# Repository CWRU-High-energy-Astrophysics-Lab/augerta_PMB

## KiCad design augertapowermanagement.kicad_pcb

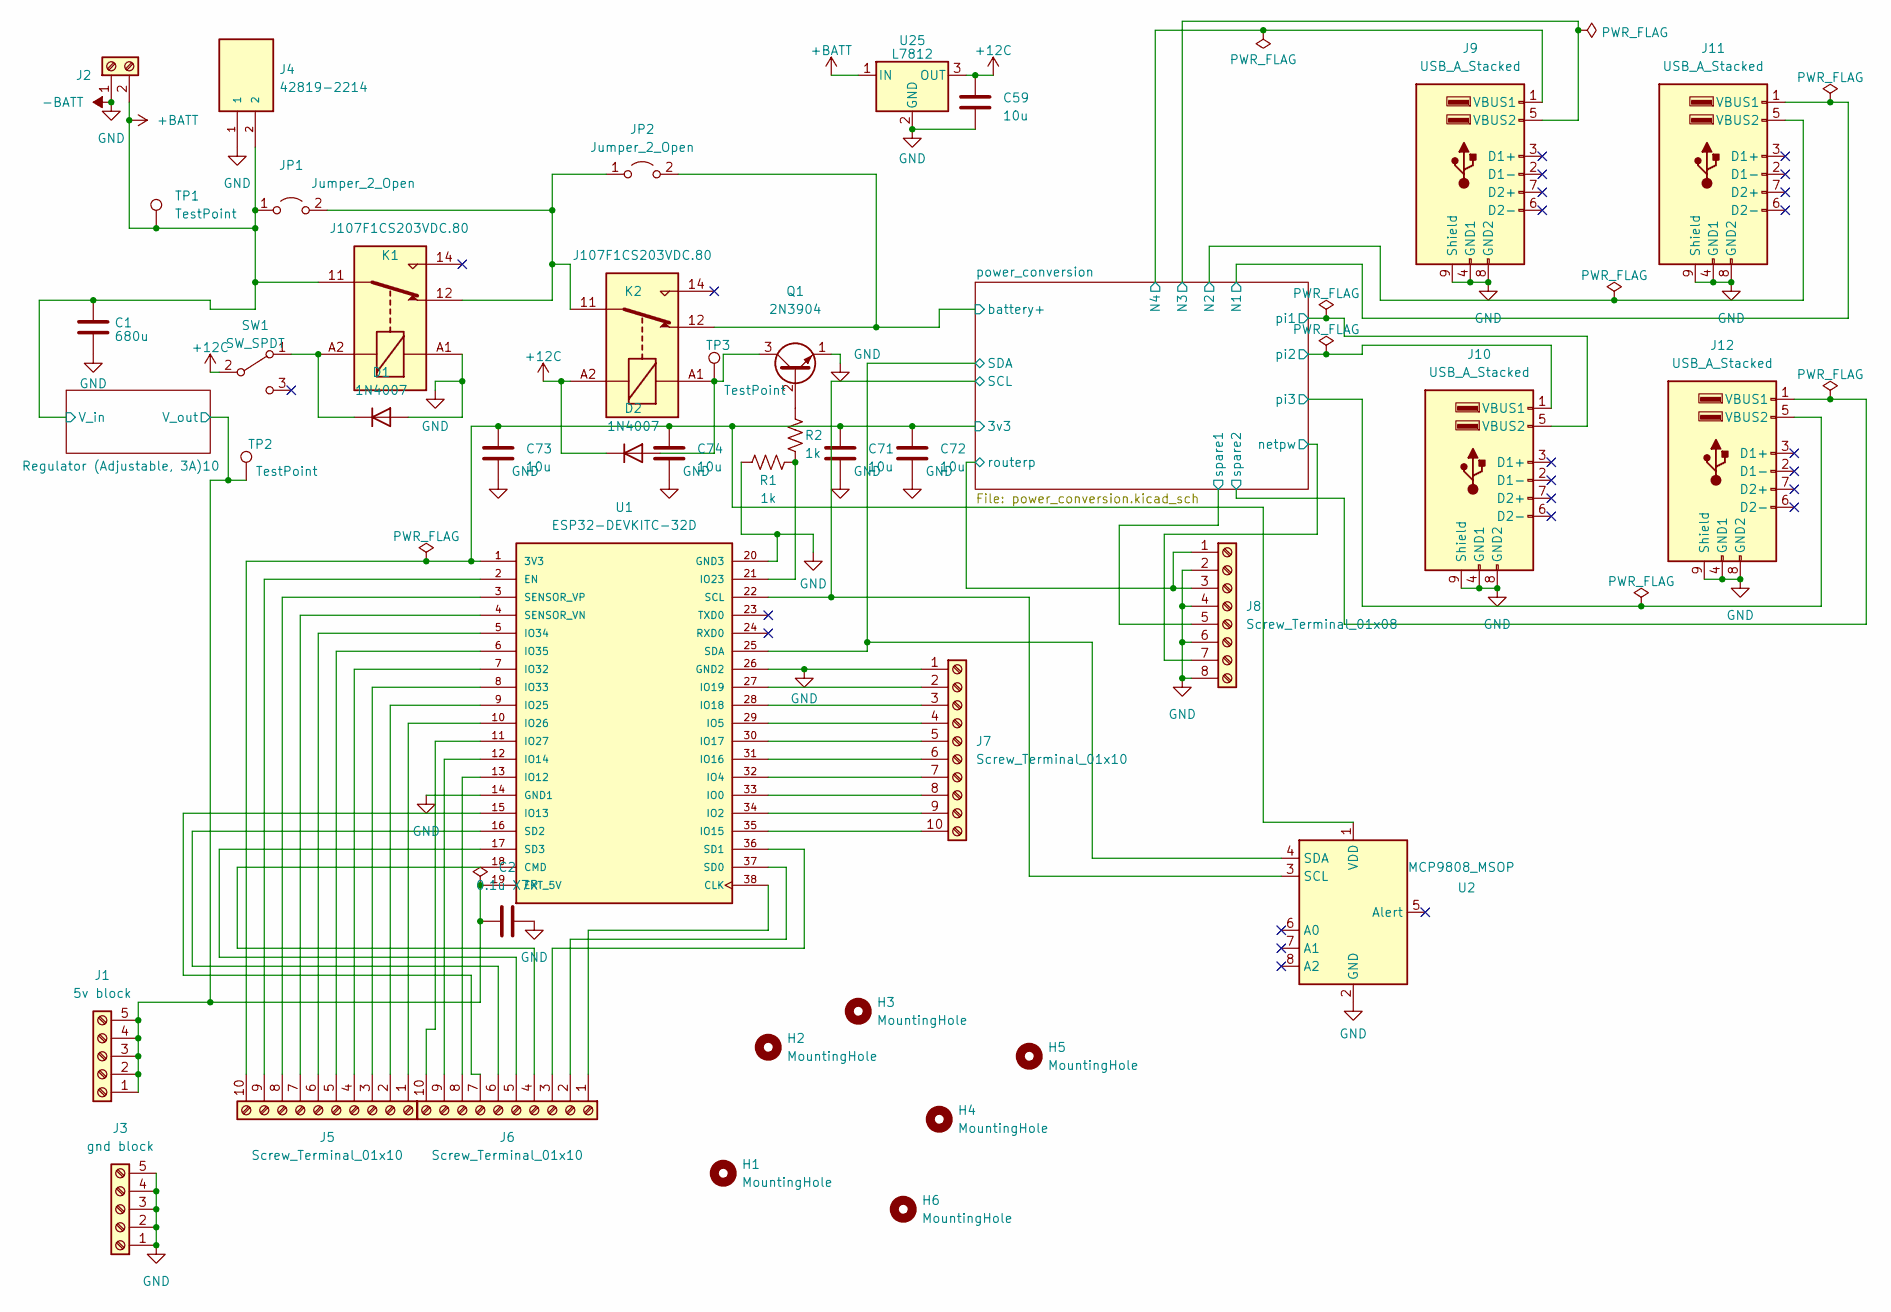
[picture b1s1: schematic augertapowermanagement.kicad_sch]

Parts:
C1: 680u; CP_Radial_D35.0mm_P10.00mm_SnapIn
C2: 0.1u X7R; C_1210_3225Metric_Pad1.33x2.70mm_HandSolder
C59, C71, C72, C73, C74: 10u; C_1210_3225Metric_Pad1.33x2.70mm_HandSolder
D1, D2: 1N4007; D_DO-41_SOD81_P10.16mm_Horizontal
H1, H2, H3, H4, H5, H6: MountingHole; MountingHole_2.5mm
J1: 5v block; TerminalBlock_Phoenix_MKDS-1,5-5-5.08_1x05_P5.08mm_Horizont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
J2: Battery in; TerminalBlock_Phoenix_MKDS-1,5-2-5.08_1x02_P5.08mm_Horizont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
J3: gnd block; TerminalBlock_Phoenix_MKDS-1,5-5-5.08_1x05_P5.08mm_Horizont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
J4: 42819-2214; Molex_Mini-Fit_Sr_42819-22XX_1x02_P10.00mm_Vertical_Thermal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; PARTREV D
J5, J6, J7: Screw_Terminal_01x10; TerminalBlock_Phoenix_MKDS-1,5-10-5.08_1x10_P5.08mm_Horizon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
J8: Screw_Terminal_01x08; TerminalBlock_Phoenix_PT-1,5-8-5.0-H_1x08_P5.00mm_Horizontal
J9, J10, J11, J12: USB_A_Stacked; USB_A_Wuerth_61400826021_Horizontal_Stacked
JP1, JP2: Jumper_2_Open; JUMPER_5102TR
K1, K2: J107F1CS203VDC.80; Relay_SPDT_RAYEX-L90S
Q1: 2N3904; TO-92_HandSolder
R1, R2: 1k; R_1206_3216Metric_Pad1.30x1.75mm_HandSolder
SW1: SW_SPDT; SW_CuK_OS102011MA1QN1_SPDT_Angled
TP1, TP2, TP3: TestPoint; TestPoint_Plated_Hole_D2.0mm
U1: ESP32-DEVKITC-32D; MODULE_ESP32-DEVKITC-32D; PARTREV 4
U2: MCP9808_MSOP; PinSocket_1x08_P2.54mm_Vertical
U25: L7812; TO-220-3_Horizontal_TabDown

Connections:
+12C: C59.1, D2.1 (K), K2.A2, SW1.2 (B), U25.3 (OUT)
-BATT: C1.2, C2.2, C59.2, C71.2, C72.2, C73.2, C74.2, D1.2 (A), J2.1, J3.1, J3.2, J3.3, J3.4, J3.5, J4.1, J7.1, J8.2, J8.4, J8.6, J8.8, J9.4 (GND1), J9.8 (GND2), J9.9 (Shield), J10.4 (GND1), J10.8 (GND2), J10.9 (Shield), J11.4 (GND1), J11.8 (GND2), J11.9 (Shield), J12.4 (GND1), J12.8 (GND2), J12.9 (Shield), K1.A1, Q1.1 (E), R1.1, U1.14 (GND1), U1.20 (GND3), U1.26 (GND2), U2.2 (GND), U25.2 (GND); also elsewhere on the board
/Regulator (Adjustable, 3A)10/V_out: C2.1, J1.1, J1.2, J1.3, J1.4, J1.5, TP2.1, U1.19 (EXT_5V); also elsewhere on the board
/power_conversion/3v3: C71.1, C72.1, C73.1, C74.1, J5.10, U1.1 (3V3), U2.1 (VDD); also elsewhere on the board
/power_conversion/N1: J11.1 (VBUS1); also elsewhere on the board
/power_conversion/N2: J11.5 (VBUS2); also elsewhere on the board
/power_conversion/N3: J9.5 (VBUS2); also elsewhere on the board
/power_conversion/N4: J9.1 (VBUS1); also elsewhere on the board
/power_conversion/SCL: U1.22 (SCL), U2.3 (SCL); also elsewhere on the board
/power_conversion/SDA: U1.25 (SDA), U2.4 (SDA); also elsewhere on the board
/power_conversion/netpw: J8.7; also elsewhere on the board
/power_conversion/pi1: J10.5 (VBUS2); also elsewhere on the board
/power_conversion/pi2: J10.1 (VBUS1); also elsewhere on the board
/power_conversion/pi3: J12.5 (VBUS2); also elsewhere on the board
/power_conversion/routerp: J8.1, J8.3; also elsewhere on the board
/power_conversion/spare1: J8.5; also elsewhere on the board
/power_conversion/spare2: J12.1 (VBUS1); also elsewhere on the board
unnamed: D1.1 (K), K1.A2, SW1.1 (A)
unnamed: D2.2 (A), K2.A1, Q1.3 (C), TP3.1
unnamed: J5.1, U1.10 (IO26)
unnamed: J5.2, U1.9 (IO25)
unnamed: J5.3, U1.8 (IO33)
unnamed: J5.4, U1.7 (IO32)
unnamed: J5.5, U1.6 (IO35)
unnamed: J5.6, U1.5 (IO34)
unnamed: J5.7, U1.4 (SENSOR_VN)
unnamed: J5.8, U1.3 (SENSOR_VP)
unnamed: J5.9, U1.2 (EN)
unnamed: J6.1, U1.38 (CLK)
unnamed: J6.2, U1.37 (SD0)
unnamed: J6.3, U1.36 (SD1)
unnamed: J6.4, U1.18 (CMD)
unnamed: J6.5, U1.17 (SD3)
unnamed: J6.6, U1.16 (SD2)
unnamed: J6.7, U1.15 (IO13)
unnamed: J6.8, U1.13 (IO12)
unnamed: J6.9, U1.12 (IO14)
unnamed: J6.10, U1.11 (IO27)
unnamed: J7.2, U1.27 (IO19)
unnamed: J7.3, U1.28 (IO18)
unnamed: J7.4, U1.29 (IO5)
unnamed: J7.5, U1.30 (IO17)
unnamed: J7.6, U1.31 (IO16)
unnamed: J7.7, U1.32 (IO4)
unnamed: J7.8, U1.33 (IO0)
unnamed: J7.9, U1.34 (IO2)
unnamed: J7.10, U1.35 (IO15)
unnamed: JP1.2 (B), JP2.1 (A), K1.12, K2.11
unnamed: Q1.2 (B), R2.2
unnamed: R1.2, R2.1, U1.21 (IO23)

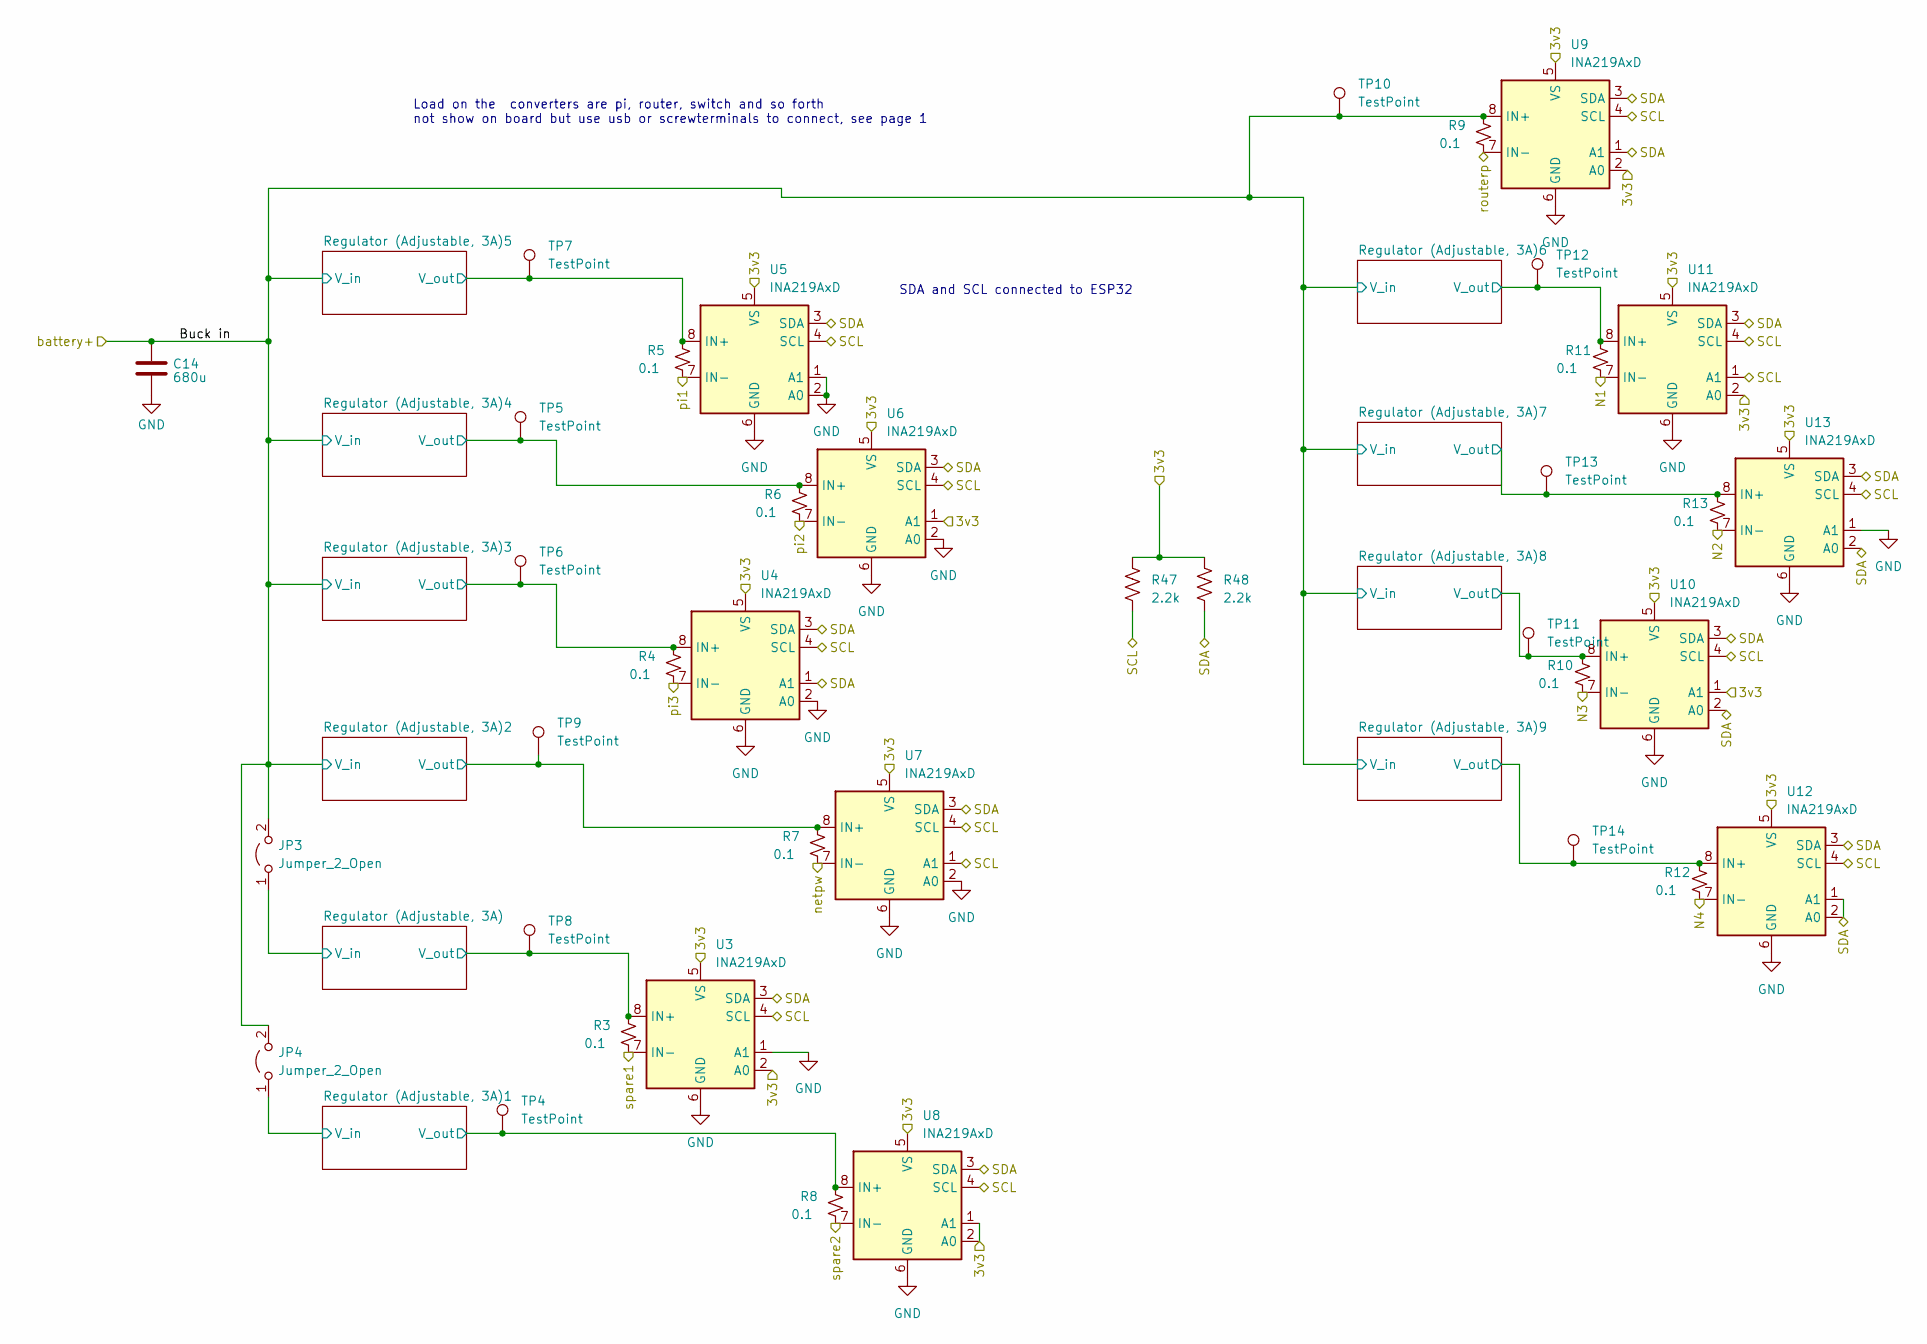
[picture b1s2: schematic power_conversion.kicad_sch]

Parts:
C14: 680u; CP_Radial_D35.0mm_P10.00mm_SnapIn
JP3, JP4: Jumper_2_Open; PinHeader_1x02_P2.00mm_Horizontal
R3, R4, R5, R6, R7, R8, R9, R10, R11, R12, R13: 0.1; R_2816_7142Metric_Pad3.20x4.45mm_HandSolder
R47, R48: 2.2k; R_1210_3225Metric_Pad1.30x2.65mm_HandSolder
TP4, TP5, TP6, TP7, TP8, TP9, TP10, TP11, TP12, TP13, TP14: TestPoint; TestPoint_Plated_Hole_D2.0mm
U3, U4, U5, U6, U7, U8, U9, U10, U11, U12, U13: INA219AxD; SOIC-8_3.9x4.9mm_P1.27mm

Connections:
-BATT: C14.2, U3.1 (A1), U3.6 (GND), U4.2 (A0), U4.6 (GND), U5.1 (A1), U5.2 (A0), U5.6 (GND), U6.2 (A0), U6.6 (GND), U7.2 (A0), U7.6 (GND), U8.6 (GND), U9.6 (GND), U10.6 (GND), U11.6 (GND), U12.6 (GND), U13.1 (A1), U13.6 (GND); also elsewhere on the board
/power_conversion/3v3: R47.1, R48.1, U3.2 (A0), U3.5 (VS), U4.5 (VS), U5.5 (VS), U6.1 (A1), U6.5 (VS), U7.5 (VS), U8.1 (A1), U8.2 (A0), U8.5 (VS), U9.2 (A0), U9.5 (VS), U10.1 (A1), U10.5 (VS), U11.2 (A0), U11.5 (VS), U12.5 (VS), U13.5 (VS); also elsewhere on the board
/power_conversion/N1: R11.1, U11.7 (IN-); also elsewhere on the board
/power_conversion/N2: R13.1, U13.7 (IN-); also elsewhere on the board
/power_conversion/N3: R10.1, U10.7 (IN-); also elsewhere on the board
/power_conversion/N4: R12.1, U12.7 (IN-); also elsewhere on the board
/power_conversion/Regulator (Adjustable, 3A)1/V_in: JP4.1 (A); also elsewhere on the board
/power_conversion/Regulator (Adjustable, 3A)1/V_out: R8.2, TP4.1, U8.8 (IN+); also elsewhere on the board
/power_conversion/Regulator (Adjustable, 3A)2/V_out: R7.2, TP9.1, U7.8 (IN+); also elsewhere on the board
/power_conversion/Regulator (Adjustable, 3A)3/V_out: R4.2, TP6.1, U4.8 (IN+); also elsewhere on the board
/power_conversion/Regulator (Adjustable, 3A)5/V_out: R5.2, TP7.1, U5.8 (IN+); also elsewhere on the board
/power_conversion/Regulator (Adjustable, 3A)6/V_out: R11.2, TP12.1, U11.8 (IN+); also elsewhere on the board
/power_conversion/Regulator (Adjustable, 3A)7/V_out: R13.2, TP13.1, U13.8 (IN+); also elsewhere on the board
/power_conversion/Regulator (Adjustable, 3A)8/V_out: R10.2, TP11.1, U10.8 (IN+); also elsewhere on the board
/power_conversion/Regulator (Adjustable, 3A)9/V_out: R12.2, TP14.1, U12.8 (IN+); also elsewhere on the board
/power_conversion/Regulator (Adjustable, 3A)/V_in: JP3.1 (A); also elsewhere on the board
/power_conversion/Regulator (Adjustable, 3A)/V_out: R3.2, TP8.1, U3.8 (IN+); also elsewhere on the board
/power_conversion/SCL: R47.2, U3.4 (SCL), U4.4 (SCL), U5.4 (SCL), U6.4 (SCL), U7.1 (A1), U7.4 (SCL), U8.4 (SCL), U9.4 (SCL), U10.4 (SCL), U11.1 (A1), U11.4 (SCL), U12.4 (SCL), U13.4 (SCL); also elsewhere on the board
/power_conversion/SDA: R48.2, U3.3 (SDA), U4.1 (A1), U4.3 (SDA), U5.3 (SDA), U6.3 (SDA), U7.3 (SDA), U8.3 (SDA), U9.1 (A1), U9.3 (SDA), U10.2 (A0), U10.3 (SDA), U11.3 (SDA), U12.1 (A1), U12.2 (A0), U12.3 (SDA), U13.2 (A0), U13.3 (SDA); also elsewhere on the board
/power_conversion/netpw: R7.1, U7.7 (IN-); also elsewhere on the board
/power_conversion/pi1: R5.1, U5.7 (IN-); also elsewhere on the board
/power_conversion/pi2: R6.1, U6.7 (IN-); also elsewhere on the board
/power_conversion/pi3: R4.1, U4.7 (IN-); also elsewhere on the board
/power_conversion/routerp: R9.1, U9.7 (IN-); also elsewhere on the board
/power_conversion/spare1: R3.1, U3.7 (IN-); also elsewhere on the board
/power_conversion/spare2: R8.1, U8.7 (IN-); also elsewhere on the board

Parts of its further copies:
C3: 680u; CP_Radial_D35.0mm_P10.00mm_SnapIn

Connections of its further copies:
-BATT: C3.2; also elsewhere on the board

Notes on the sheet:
Load on the converters are pi, router, switch and so forth not show on board but use usb or screwterminals to connect, see page 1
SDA and SCL connected to ESP32

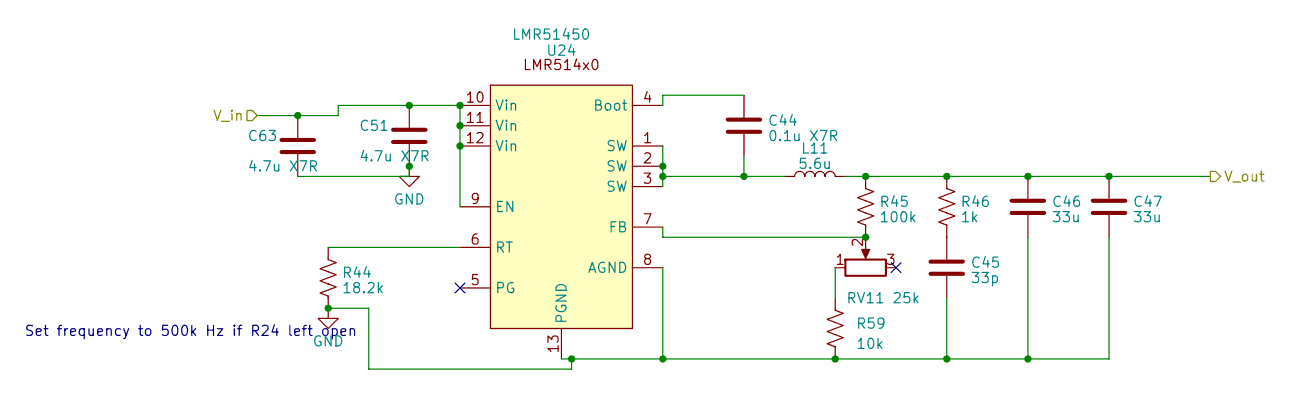
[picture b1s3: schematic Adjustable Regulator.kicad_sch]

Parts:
C44: 0.1u X7R; C_1210_3225Metric_Pad1.33x2.70mm_HandSolder
C45: 33p; C_1210_3225Metric_Pad1.33x2.70mm_HandSolder
C46, C47: 33u; C_1206_3216Metric_Pad1.33x1.80mm_HandSolder
C51, C63: 4.7u X7R; C_1210_3225Metric_Pad1.33x2.70mm_HandSolder
L11: 5.6u; L_Bourns_SRP1770TA_16.9x16.9mm
R44: 18.2k; R_1206_3216Metric_Pad1.30x1.75mm_HandSolder
R45: 100k; R_1206_3216Metric_Pad1.30x1.75mm_HandSolder
R46: 1k; R_1206_3216Metric_Pad1.30x1.75mm_HandSolder
R59: 10k; R_1206_3216Metric_Pad1.30x1.75mm_HandSolder
RV11: 25k; Potentiometer_Bourns_3314J_Vertical
U24: LMR51450; WSON_SDRRR_TEX-M

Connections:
-BATT: C45.2, C46.2, C47.2, C51.2, C63.2, R44.2, R59.2, U24.8 (AGND), U24.13 (PGND); also elsewhere on the board
/Regulator (Adjustable, 3A)10/V_out: C46.1, C47.1, L11.2, R45.1, R46.1; also elsewhere on the board
unnamed: C44.2, L11.1, U24.1 (SW), U24.2 (SW), U24.3 (SW)
unnamed: C45.1, R46.2
unnamed: R59.1, RV11.1
unnamed: C44.1, U24.4 (Boot)
unnamed: R45.2, RV11.2, U24.7 (FB)
unnamed: R44.1, U24.6 (RT)

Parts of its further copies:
C4, C8, C12, C16, C20, C24, C28, C32, C36, C40: 0.1u X7R; C_1210_3225Metric_Pad1.33x2.70mm_HandSolder
C5, C9, C13, C17, C21, C25, C29, C33, C37, C41: 33p; C_1210_3225Metric_Pad1.33x2.70mm_HandSolder
C6, C7, C10, C11, C15, C18, C19, C22, C23, C26, C27, C30, C31, C34, C35, C38, C39, C42, C43: 33u; C_1206_3216Metric_Pad1.33x1.80mm_HandSolder
C48, C49, C50, C52, C53, C54, C55, C56, C57, C58, C60, C61, C62, C64, C65, C66, C67, C68, C69, C70: 4.7u X7R; C_1210_3225Metric_Pad1.33x2.70mm_HandSolder
L1, L2, L3, L4, L5, L6, L7, L8, L9, L10: 5.6u; L_Bourns_SRP1770TA_16.9x16.9mm
R14, R17, R20, R23, R26, R29, R32, R35, R38, R41: 18.2k; R_1206_3216Metric_Pad1.30x1.75mm_HandSolder
R15, R18, R21, R24, R27, R30, R33, R36, R39, R42: 100k; R_1206_3216Metric_Pad1.30x1.75mm_HandSolder
R16, R19, R22, R25, R28, R31, R34, R37, R40, R43: 1k; R_1206_3216Metric_Pad1.30x1.75mm_HandSolder
R49, R50, R51, R52, R53, R54, R55, R56, R57, R58: 10k; R_1206_3216Metric_Pad1.30x1.75mm_HandSolder
RV1, RV2, RV3, RV4, RV5, RV6, RV7, RV8, RV9, RV10: 25k; Potentiometer_Bourns_3314J_Vertical
U14, U15, U16, U17, U18, U19, U20, U21, U22, U23: LMR51450; WSON_SDRRR_TEX-M

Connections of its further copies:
-BATT: C5.2, C6.2, C7.2, C9.2, C10.2, C11.2, C13.2, C15.2, C17.2, C18.2, C19.2, C21.2, C22.2, C23.2, C25.2, C26.2, C27.2, C29.2, C30.2, C31.2, C33.2, C34.2, C35.2, C37.2, C38.2, C39.2, C41.2, C42.2, C43.2, C48.2, C49.2, C50.2, C52.2, C53.2, C54.2, C55.2, C56.2, C57.2, C58.2, C60.2, C61.2, C62.2, C64.2, C65.2, C66.2, C67.2, C68.2, C69.2, C70.2, R14.2, R17.2, R20.2, R23.2, R26.2, R29.2, R32.2, R35.2, R38.2, R41.2, R49.2, R50.2, R51.2, R52.2, R53.2, R54.2, R55.2, R56.2, R57.2, R58.2, U14.8 (AGND), U14.13 (PGND), U15.8 (AGND), U15.13 (PGND), U16.8 (AGND), U16.13 (PGND), U17.8 (AGND), U17.13 (PGND), U18.8 (AGND), U18.13 (PGND), U19.8 (AGND), U19.13 (PGND), U20.8 (AGND), U20.13 (PGND), U21.8 (AGND), U21.13 (PGND), U22.8 (AGND), U22.13 (PGND), U23.8 (AGND), U23.13 (PGND); also elsewhere on the board
/power_conversion/Regulator (Adjustable, 3A)1/V_in: C57.1, C69.1, U23.9 (EN), U23.10 (Vin), U23.11 (Vin), U23.12 (Vin); also elsewhere on the board
/power_conversion/Regulator (Adjustable, 3A)1/V_out: C42.1, C43.1, L10.2, R42.1, R43.1; also elsewhere on the board
/power_conversion/Regulator (Adjustable, 3A)2/V_out: C6.1, C7.1, L1.2, R15.1, R16.1; also elsewhere on the board
/power_conversion/Regulator (Adjustable, 3A)3/V_out: C10.1, C11.1, L2.2, R18.1, R19.1; also elsewhere on the board
/power_conversion/Regulator (Adjustable, 3A)5/V_out: C18.1, C19.1, L4.2, R24.1, R25.1; also elsewhere on the board
/power_conversion/Regulator (Adjustable, 3A)6/V_out: C22.1, C23.1, L5.2, R27.1, R28.1; also elsewhere on the board
/power_conversion/Regulator (Adjustable, 3A)7/V_out: C26.1, C27.1, L6.2, R30.1, R31.1; also elsewhere on the board
/power_conversion/Regulator (Adjustable, 3A)8/V_out: C30.1, C31.1, L7.2, R33.1, R34.1; also elsewhere on the board
/power_conversion/Regulator (Adjustable, 3A)9/V_out: C34.1, C35.1, L8.2, R36.1, R37.1; also elsewhere on the board
/power_conversion/Regulator (Adjustable, 3A)/V_in: C56.1, C68.1, U22.9 (EN), U22.10 (Vin), U22.11 (Vin), U22.12 (Vin); also elsewhere on the board
/power_conversion/Regulator (Adjustable, 3A)/V_out: C38.1, C39.1, L9.2, R39.1, R40.1; also elsewhere on the board
unnamed: C4.2, L1.1, U14.1 (SW), U14.2 (SW), U14.3 (SW)
unnamed: C5.1, R16.2
unnamed: C8.2, L2.1, U15.1 (SW), U15.2 (SW), U15.3 (SW)
unnamed: C9.1, R19.2
unnamed: C12.2, L3.1, U16.1 (SW), U16.2 (SW), U16.3 (SW)
unnamed: C13.1, R22.2
unnamed: C16.2, L4.1, U17.1 (SW), U17.2 (SW), U17.3 (SW)
unnamed: C17.1, R25.2
unnamed: C20.2, L5.1, U18.1 (SW), U18.2 (SW), U18.3 (SW)
unnamed: C21.1, R28.2
unnamed: C24.2, L6.1, U19.1 (SW), U19.2 (SW), U19.3 (SW)
unnamed: C25.1, R31.2
unnamed: C28.2, L7.1, U20.1 (SW), U20.2 (SW), U20.3 (SW)
unnamed: C29.1, R34.2
unnamed: C32.2, L8.1, U21.1 (SW), U21.2 (SW), U21.3 (SW)
unnamed: C33.1, R37.2
unnamed: C36.2, L9.1, U22.1 (SW), U22.2 (SW), U22.3 (SW)
unnamed: C37.1, R40.2
unnamed: C40.2, L10.1, U23.1 (SW), U23.2 (SW), U23.3 (SW)
unnamed: C41.1, R43.2
unnamed: R49.1, RV1.1
unnamed: R50.1, RV2.1
unnamed: R51.1, RV3.1
unnamed: R52.1, RV4.1
unnamed: R53.1, RV5.1
unnamed: R54.1, RV6.1
unnamed: R55.1, RV7.1
unnamed: R56.1, RV8.1
unnamed: R57.1, RV9.1
unnamed: R58.1, RV10.1
unnamed: C4.1, U14.4 (Boot)
unnamed: R15.2, RV1.2, U14.7 (FB)
unnamed: R14.1, U14.6 (RT)
unnamed: C8.1, U15.4 (Boot)
unnamed: R18.2, RV2.2, U15.7 (FB)
unnamed: R17.1, U15.6 (RT)
unnamed: C12.1, U16.4 (Boot)
unnamed: R21.2, RV3.2, U16.7 (FB)
unnamed: R20.1, U16.6 (RT)
unnamed: C16.1, U17.4 (Boot)
unnamed: R24.2, RV4.2, U17.7 (FB)
unnamed: R23.1, U17.6 (RT)
unnamed: C20.1, U18.4 (Boot)
unnamed: R27.2, RV5.2, U18.7 (FB)
unnamed: R26.1, U18.6 (RT)
unnamed: C24.1, U19.4 (Boot)
unnamed: R30.2, RV6.2, U19.7 (FB)
unnamed: R29.1, U19.6 (RT)
unnamed: C28.1, U20.4 (Boot)
unnamed: R33.2, RV7.2, U20.7 (FB)
unnamed: R32.1, U20.6 (RT)
unnamed: C32.1, U21.4 (Boot)
unnamed: R36.2, RV8.2, U21.7 (FB)
unnamed: R35.1, U21.6 (RT)
unnamed: C36.1, U22.4 (Boot)
unnamed: R39.2, RV9.2, U22.7 (FB)
unnamed: R38.1, U22.6 (RT)
unnamed: C40.1, U23.4 (Boot)
unnamed: R42.2, RV10.2, U23.7 (FB)
unnamed: R41.1, U23.6 (RT)

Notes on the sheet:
Set frequency to 500k Hz if R24 left open

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
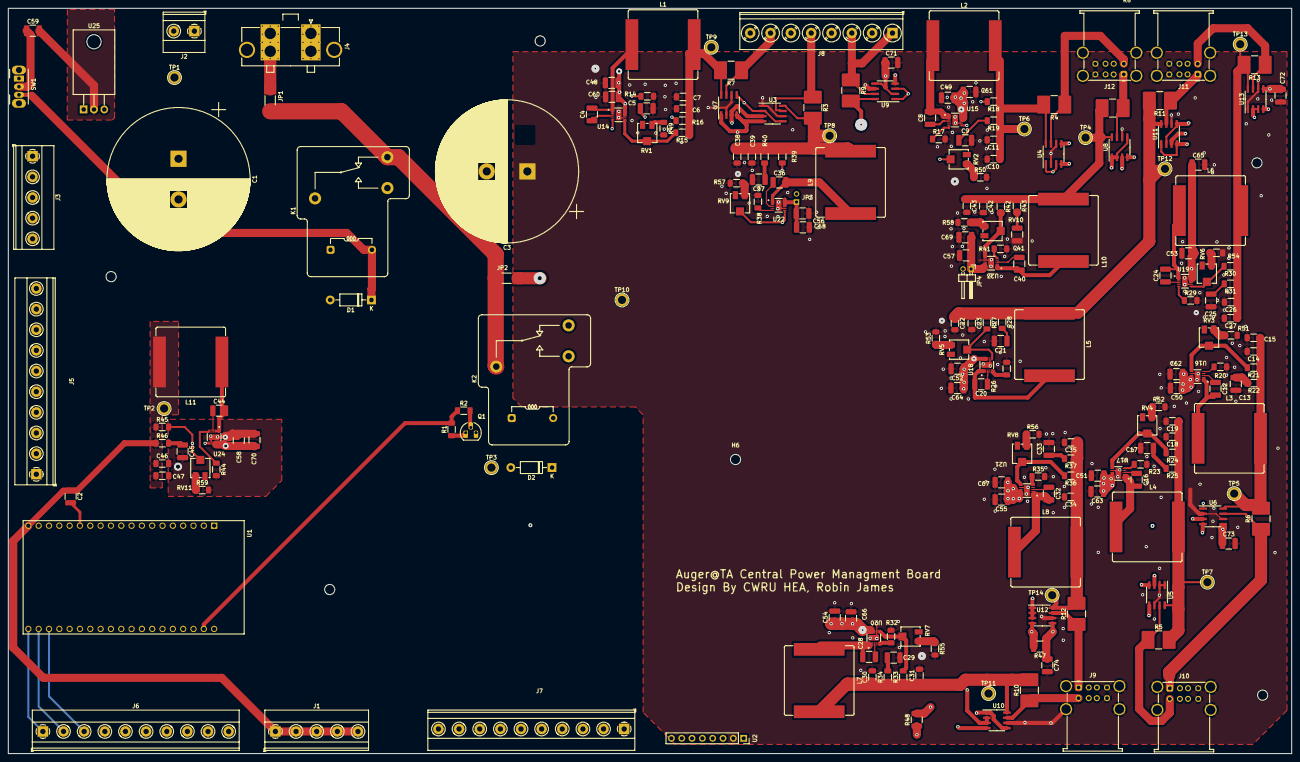
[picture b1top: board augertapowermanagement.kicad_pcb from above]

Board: 4 copper layers, 315.8 x 183.4 mm, 222 parts (1 on the bottom side), 130 nets.

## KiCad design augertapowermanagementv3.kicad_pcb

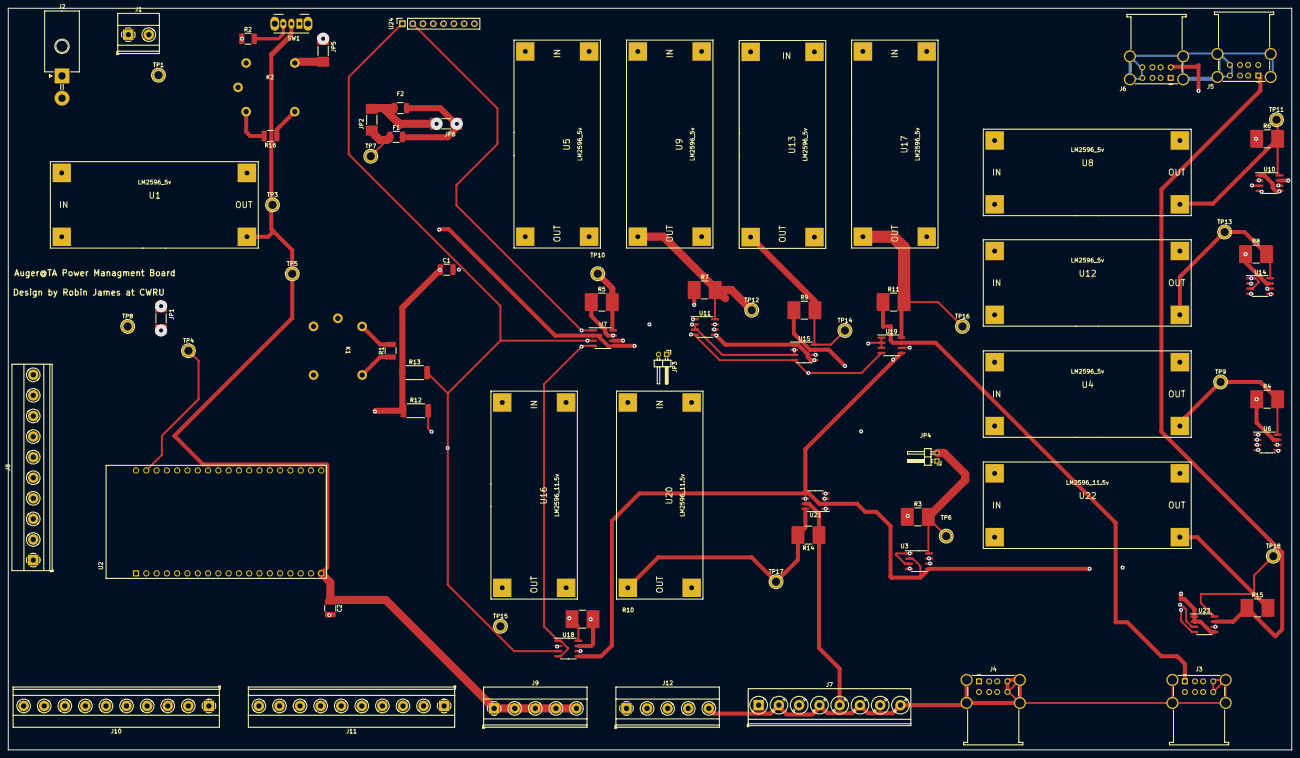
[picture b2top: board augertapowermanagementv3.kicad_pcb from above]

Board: 4 copper layers, 316.7 x 183.0 mm, 82 parts (0 on the bottom side), 67 nets.

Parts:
C1: 0.1uF; C_1210_3225Metric_Pad1.33x2.70mm_HandSolder
C2: 0.1; C_1210_3225Metric_Pad1.33x2.70mm_HandSolder
F1, F2: 1210L900SLPR; R_1210_3225Metric_Pad1.30x2.65mm_HandSolder
J1: Screw_Terminal_01x02; TerminalBlock_Phoenix_MKDS-1,5-2-5.08_1x02_P5.08mm_Horizont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
J2: 76825-0002; Molex_Mega-Fit_76825-0002_2x01_P5.70mm_Horizontal
J3, J4, J5, J6: USB_A_Stacked; USB_A_Wuerth_61400826021_Horizontal_Stacked
J7: Screw_Terminal_01x08; TerminalBlock_Phoenix_PT-1,5-8-5.0-H_1x08_P5.00mm_Horizontal
J8, J10, J11: Screw_Terminal_01x10; TerminalBlock_Phoenix_MKDS-1,5-10-5.08_1x10_P5.08mm_Horizon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
J9: 5v block; TerminalBlock_Phoenix_MKDS-1,5-5-5.08_1x05_P5.08mm_Horizont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
J12: gnd block; TerminalBlock_Phoenix_MKDS-1,5-5-5.08_1x05_P5.08mm_Horizont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
JP1, JP2, JP5, JP6: Jumper_2_Open; JUMPER_5102TR
JP3, JP4: Jumper_2_Open; PinHeader_1x02_P2.00mm_Horizontal
K1, K2: J107F1CS203VDC.80; Relay_J107F
R1, R2, R16: 10k; R_1210_3225Metric_Pad1.30x2.65mm_HandSolder
R3, R4, R5, R6, R7, R8, R9, R10, R11, R14, R15: 0.1; R_2816_7142Metric_Pad3.20x4.45mm_HandSolder
R12, R13: 3.3K; R_2512_6332Metric_Pad1.40x3.35mm_HandSolder
SW1: SW_SPDT; SW_CuK_OS102011MA1QN1_SPDT_Angled
TP1, TP3, TP4, TP5, TP6, TP7, TP8, TP9, TP10, TP11, TP12, TP13, TP14, TP15, TP16, TP17, TP18: TestPoint; TestPoint_Plated_Hole_D2.0mm
U1, U4, U5, U8, U9, U12, U13, U17: LM2596_5v; DC_DC_LM2596_small
U2: ESP32-DEVKITC-32D; MODULE_ESP32-DEVKITC-32D
U3, U6, U7, U10, U11, U14, U15, U18, U19, U21, U23: INA219AxD; SOIC-8_3.9x4.9mm_P1.27mm
U16, U20, U22: LM2596_11.5v; DC_DC_LM2596_small
U24: MCP9808_MSOP; PinSocket_1x08_P2.54mm_Vertical

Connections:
+BATT: J1.2, J2.2, JP5.1 (A), K2.7, TP1.1, U1.1 (Vin)
-BATT: C1.2, C2.2, J1.1, J2.1, J3.4 (GND1), J3.8 (GND2), J3.9 (Shield), J4.4 (GND1), J4.8 (GND2), J4.9 (Shield), J5.4 (GND1), J5.8 (GND2), J5.9 (Shield), J6.4 (GND1), J6.8 (GND2), J6.9 (Shield), J7.2, J7.4, J7.6, J7.8, J12.1, J12.2, J12.3, J12.4, J12.5, K1.2, K2.6, R1.2, R2.1, R16.2, U1.2 (GND), U1.3 (GND), U2.14 (GND1), U3.6 (GND), U4.2 (GND), U4.3 (GND), U5.2 (GND), U5.3 (GND), U6.1 (A1), U6.2 (A0), U6.6 (GND), U7.6 (GND), U8.2 (GND), U8.3 (GND), U9.2 (GND), U9.3 (GND), U10.2 (A0), U10.6 (GND), U11.1 (A1), U11.6 (GND), U12.2 (GND), U12.3 (GND), U13.2 (GND), U13.3 (GND), U14.2 (A0), U14.6 (GND), U15.6 (GND), U16.2 (GND), U16.3 (GND), U17.2 (GND), U17.3 (GND), U18.2 (A0), U18.6 (GND), U19.6 (GND), U20.2 (GND), U20.3 (GND), U21.1 (A1), U21.6 (GND), U22.2 (GND), U22.3 (GND), U23.6 (GND), U24.4 (GND)
/power_conversion/N1: J4.1 (VBUS1), R5.1, U7.7 (IN-)
/power_conversion/N2: J4.5 (VBUS2), R7.1, U11.7 (IN-)
/power_conversion/N3: J3.5 (VBUS2), R9.1, U15.7 (IN-)
/power_conversion/N4: J3.1 (VBUS1), R11.1, U19.7 (IN-)
/power_conversion/SCL: R12.2, U2.22 (SCL), U3.4 (SCL), U6.4 (SCL), U7.1 (A1), U7.4 (SCL), U10.4 (SCL), U11.4 (SCL), U14.4 (SCL), U15.4 (SCL), U18.1 (A1), U18.4 (SCL), U19.4 (SCL), U21.4 (SCL), U23.4 (SCL), U24.2 (SCL)
/power_conversion/SDA: R13.2, U2.25 (SDA), U3.1 (A1), U3.3 (SDA), U6.3 (SDA), U7.3 (SDA), U10.3 (SDA), U11.2 (A0), U11.3 (SDA), U14.1 (A1), U14.3 (SDA), U15.2 (A0), U15.3 (SDA), U18.3 (SDA), U19.1 (A1), U19.2 (A0), U19.3 (SDA), U21.3 (SDA), U23.3 (SDA), U24.1 (SDA)
/power_conversion/battery+: F2.1, JP1.2 (B), JP2.2 (B), JP6.2 (B), K1.1, TP8.1
/power_conversion/netpw: J7.7, R10.1, U18.7 (IN-)
/power_conversion/pi1: J6.5 (VBUS2), R4.1, U6.7 (IN-)
/power_conversion/pi2: J6.1 (VBUS1), R6.1, U10.7 (IN-)
/power_conversion/pi3: J5.5 (VBUS2), R8.1, U14.7 (IN-)
/power_conversion/pi 5v: C1.1, J10.10, R12.1, R13.1, U2.1 (3V3), U3.2 (A0), U3.5 (VS), U6.5 (VS), U7.2 (A0), U7.5 (VS), U10.1 (A1), U10.5 (VS), U11.5 (VS), U14.5 (VS), U15.1 (A1), U15.5 (VS), U18.5 (VS), U19.5 (VS), U21.2 (A0), U21.5 (VS), U23.1 (A1), U23.2 (A0), U23.5 (VS), U24.8 (VDD)
/power_conversion/routerp: J7.3, R3.1, U3.7 (IN-)
/power_conversion/spare1: J7.5, R14.1, U21.7 (IN-)
/power_conversion/spare2: J5.1 (VBUS1), R15.1, U23.7 (IN-)
unnamed: C2.1, J9.1, J9.2, J9.3, J9.4, J9.5, SW1.2 (B), TP3.1, TP5.1, U1.4 (Vout), U2.19 (EXT_5V)
unnamed: F1.1, JP2.1 (A), TP7.1
unnamed: F1.2, F2.2, JP3.2 (B), JP4.2 (B), JP6.1 (A), R3.2, TP6.1, U3.8 (IN+), U4.1 (Vin), U5.1 (Vin), U8.1 (Vin), U9.1 (Vin), U12.1 (Vin), U13.1 (Vin), U16.1 (Vin), U17.1 (Vin)
unnamed: J8.1, U2.26 (GND2)
unnamed: J8.2, U2.27 (IO19)
unnamed: J8.3, U2.28 (IO18)
unnamed: J8.4, U2.29 (IO5)
unnamed: J8.5, U2.30 (IO17)
unnamed: J8.6, U2.31 (IO16)
unnamed: J8.7, U2.32 (IO4)
unnamed: J8.8, U2.33 (IO0)
unnamed: J8.9, U2.34 (IO2)
unnamed: J8.10, U2.35 (IO15)
unnamed: J10.1, U2.10 (IO26)
unnamed: J10.2, U2.9 (IO25)
unnamed: J10.3, U2.8 (IO33)
unnamed: J10.4, U2.7 (IO32)
unnamed: J10.5, U2.6 (IO35)
unnamed: J10.6, U2.5 (IO34)
unnamed: J10.7, U2.4 (SENSOR_VN)
unnamed: J10.8, U2.3 (SENSOR_VP)
unnamed: J10.9, U2.2 (EN)
unnamed: J11.1, U2.36 (SD1)
unnamed: J11.2, U2.37 (SD0)
unnamed: J11.3, U2.38 (CLK)
unnamed: J11.4, U2.18 (CMD)
unnamed: J11.5, U2.17 (SD3)
unnamed: J11.6, U2.16 (SD2)
unnamed: J11.7, U2.15 (IO13)
unnamed: J11.8, U2.13 (IO12)
unnamed: J11.9, U2.12 (IO14)
unnamed: J11.10, U2.11 (IO27)
unnamed: JP3.1 (A), U20.1 (Vin)
unnamed: JP4.1 (A), U22.1 (Vin)
unnamed: JP1.1 (A), JP5.2 (B), K1.7, K2.14
unnamed: K1.6, TP4.1, U2.21 (IO23)
unnamed: K1.14, R1.1
unnamed: K2.1, R16.1
unnamed: R4.2, TP9.1, U4.4 (Vout), U6.8 (IN+)
unnamed: R5.2, TP10.1, U5.4 (Vout), U7.8 (IN+)
unnamed: R6.2, TP11.1, U8.4 (Vout), U10.8 (IN+)
unnamed: R7.2, TP12.1, U9.4 (Vout), U11.8 (IN+)
unnamed: R8.2, TP13.1, U12.4 (Vout), U14.8 (IN+)
unnamed: R9.2, TP14.1, U13.4 (Vout), U15.8 (IN+)
unnamed: R10.2, TP15.1, U16.4 (Vout), U18.8 (IN+)
unnamed: R11.2, TP16.1, U17.4 (Vout), U19.8 (IN+)
unnamed: R14.2, TP17.1, U20.4 (Vout), U21.8 (IN+)
unnamed: R15.2, TP18.1, U22.4 (Vout), U23.8 (IN+)
unnamed: K2.2, SW1.1 (A)
unnamed: R2.2, SW1.3 (C)

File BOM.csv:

"Id";"Designator";"Package";"Quantity";"Designation";"Supplier and ref";
1;"U14,U3,U10,U15,U7,U18,U19,U6,U11,U21,U23";"SOIC-8_3.9x4.9mm_P1.27mm";11;"INA219AxD";;;
2;"J10,J8,J11";"TerminalBlock_Phoenix_MKDS-1,5-10-5.08_1x10_P5.08mm_Horizontal";3;"Screw_Terminal_01x10";;;
3;"TP6,TP9,TP12,TP7,TP3,TP5,TP16,TP15,TP1,TP17,TP13,TP18,TP10,TP8,TP14,TP4,TP11";"TestPoint_Plated_Hole_D2.0mm";17;"TestPoint";;;
4;"JP5,JP6,JP3,JP4,JP2,JP1";"PinHeader_1x02_P2.00mm_Horizontal";6;"Jumper_2_Open";;;
5;"J2";"Molex_Mega-Fit_76825-0002_2x01_P5.70mm_Horizontal";1;"76825-0002";;;
6;"U8,U9,U12,U4,U5,U13,U17,U1";"DC_DC_LM2596_small";8;"LM2596_5v";;;
7;"J9";"TerminalBlock_Phoenix_MKDS-1,5-5-5.08_1x05_P5.08mm_Horizontal";1;"5v block";;;
8;"R15,R3,R7,R5,R6,R4,R10,R8,R14,R9,R11";"R_2816_7142Metric_Pad3.20x4.45mm_HandSolder";11;"0.1";;;
9;"K1,K2";"Relay_J107F";2;"J107F1CS203VDC.80";;;
10;"C1";"C_1210_3225Metric_Pad1.33x2.70mm_HandSolder";1;"0.1uF";;;
11;"R1,R2,R16";"R_1210_3225Metric_Pad1.30x2.65mm_HandSolder";3;"10k";;;
12;"U20,U22,U16";"DC_DC_LM2596_small";3;"LM2596_11.5v";;;
13;"J1";"TerminalBlock_Phoenix_MKDS-1,5-2-5.08_1x02_P5.08mm_Horizontal";1;"Screw_Terminal_01x02";;;
14;"C2";"C_1210_3225Metric_Pad1.33x2.70mm_HandSolder";1;"0.1";;;
15;"J6,J3,J5,J4";"USB_A_Wuerth_61400826021_Horizontal_Stacked";4;"USB_A_Stacked";;;
16;"R13,R12";"R_2512_6332Metric_Pad1.40x3.35mm_HandSolder";2;"3.3K";;;
17;"SW1";"SW_CuK_OS102011MA1QN1_SPDT_Angled";1;"SW_SPDT";;;
18;"U24";"PinSocket_1x08_P2.54mm_Vertical";1;"MCP9808_MSOP";;;
19;"J12";"TerminalBlock_Phoenix_MKDS-1,5-5-5.08_1x05_P5.08mm_Horizontal";1;"gnd block";;;
20;"F1,F2";"R_1210_3225Metric_Pad1.30x2.65mm_HandSolder";2;"1210L900SLPR";;;
21;"U2";"MODULE_ESP32-DEVKITC-32D";1;"ESP32-DEVKITC-32D";;;
22;"J7";"TerminalBlock_Phoenix_PT-1,5-8-5.0-H_1x08_P5.00mm_Horizontal";1;"Screw_Terminal_01x08";;;

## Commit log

2022-08-24 Add files via upload
    upload
2022-08-24 Add files via upload
    upload2
2022-08-24 update gerber
2022-09-02 updates v4
2022-09-05 Improved power plane, relay changes, i2c resistor changes
2022-09-21 check
2022-09-22 update buck print
2023-04-13 04/13/2023
2023-05-22 finish assigning componets
2023-05-23 start pcb
2023-05-23 board progress
2023-05-24 progress
2023-06-01 draft done
2023-06-03 clean up
2023-06-04 fix lot of errors
2023-06-04 fixes
